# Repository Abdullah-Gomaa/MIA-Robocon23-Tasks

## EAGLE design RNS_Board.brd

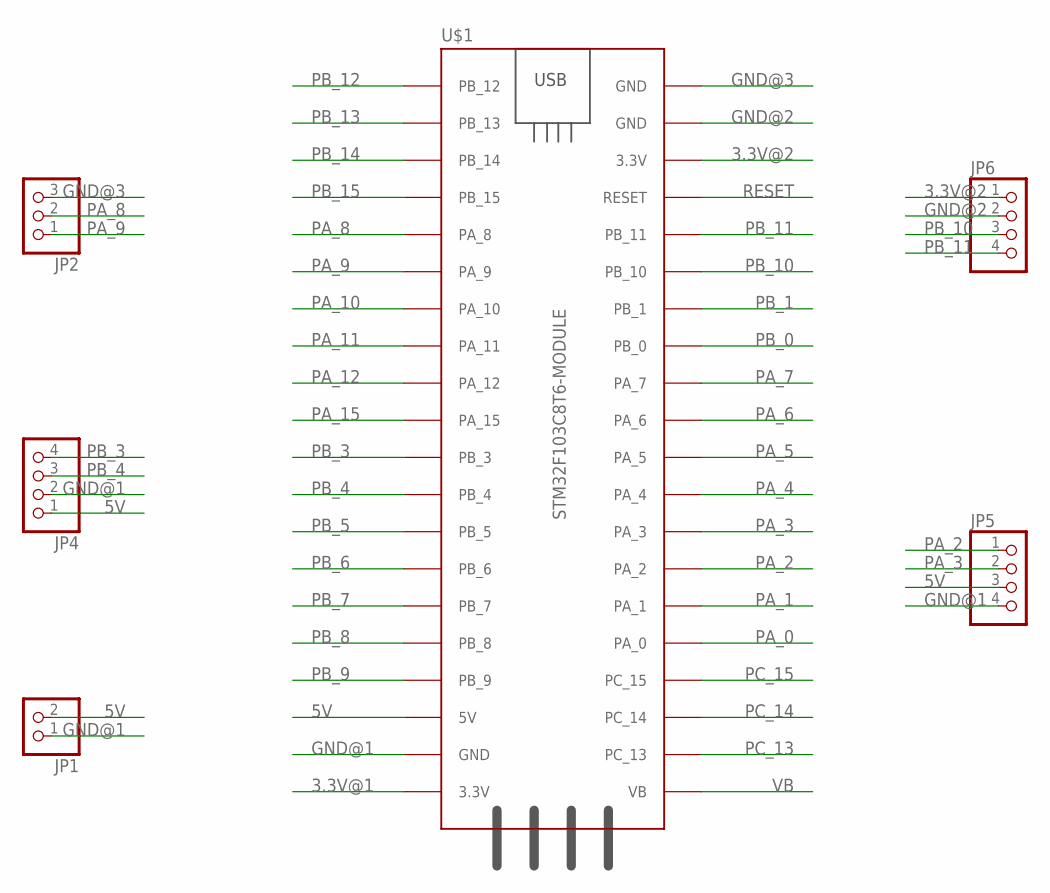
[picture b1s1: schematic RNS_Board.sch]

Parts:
JP1: PINHD-1X2; 1X02
JP2: PINHD-1X3; 1X03
JP4, JP5, JP6: PINHD-1X4; 1X04
U$1: STM32F103C8T6-MODULE

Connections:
3.3V@1: U$1.3.3V_1 (3.3V)
3.3V@2: JP6.1, U$1.3.3V_2 (3.3V)
5V: JP1.2, JP4.1, JP5.3, U$1.5V
GND@1: JP1.1, JP4.2, JP5.4, U$1.GND_1 (GND)
GND@2: JP6.2, U$1.GND_2 (GND)
GND@3: JP2.3, U$1.GND_3 (GND)
PA_0: U$1.PA_0
PA_1: U$1.PA_1
PA_2: JP5.1, U$1.PA_2
PA_3: JP5.2, U$1.PA_3
PA_4: U$1.PA_4
PA_5: U$1.PA_5
PA_6: U$1.PA_6
PA_7: U$1.PA_7
PA_8: JP2.2, U$1.PA_8
PA_9: JP2.1, U$1.PA_9
PA_10: U$1.PA_10
PA_11: U$1.PA_11
PA_12: U$1.PA_12
PA_15: U$1.PA_15
PB_0: U$1.PB_0
PB_1: U$1.PB_1
PB_3: JP4.4, U$1.PB_3
PB_4: JP4.3, U$1.PB_4
PB_5: U$1.PB_5
PB_6: U$1.PB_6
PB_7: U$1.PB_7
PB_8: U$1.PB_8
PB_9: U$1.PB_9
PB_10: JP6.3, U$1.PB_10
PB_11: JP6.4, U$1.PB_11
PB_12: U$1.PB_12
PB_13: U$1.PB_13
PB_14: U$1.PB_14
PB_15: U$1.PB_15
PC_13: U$1.PC_13
PC_14: U$1.PC_14
PC_15: U$1.PC_15
RESET: U$1.RESET
VB: U$1.VB

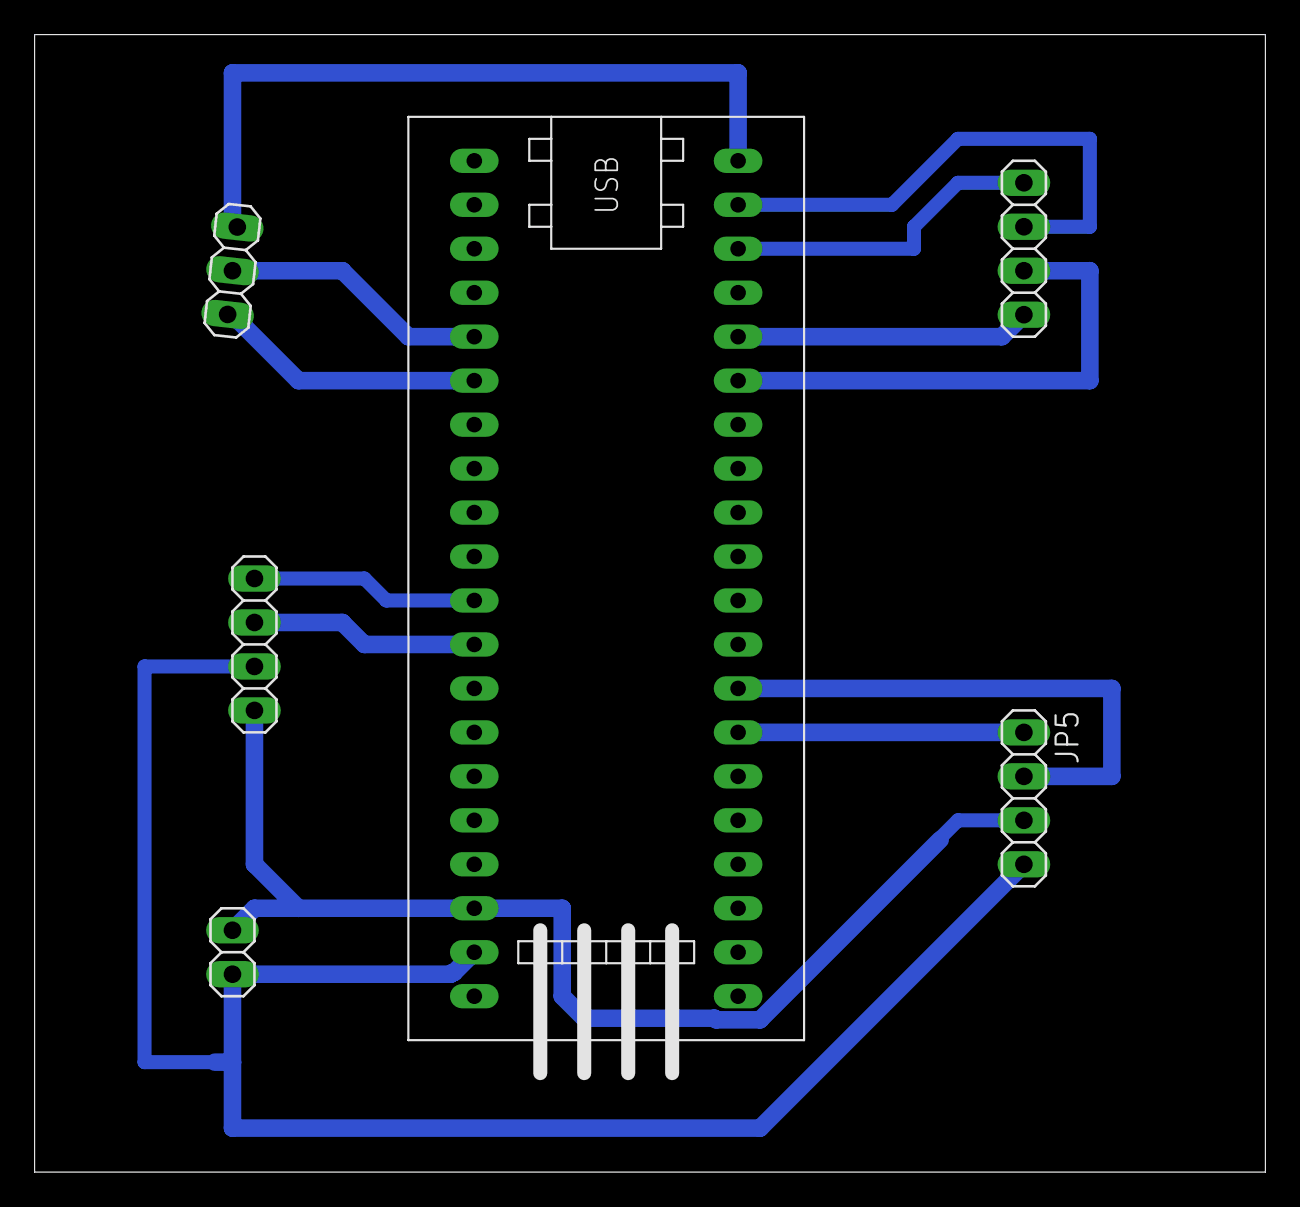
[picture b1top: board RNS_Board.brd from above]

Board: 2 copper layers, 71.1 x 65.7 mm, 6 parts (0 on the bottom side), 13 nets.

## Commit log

2022-10-10 Week 2: PCB Task
